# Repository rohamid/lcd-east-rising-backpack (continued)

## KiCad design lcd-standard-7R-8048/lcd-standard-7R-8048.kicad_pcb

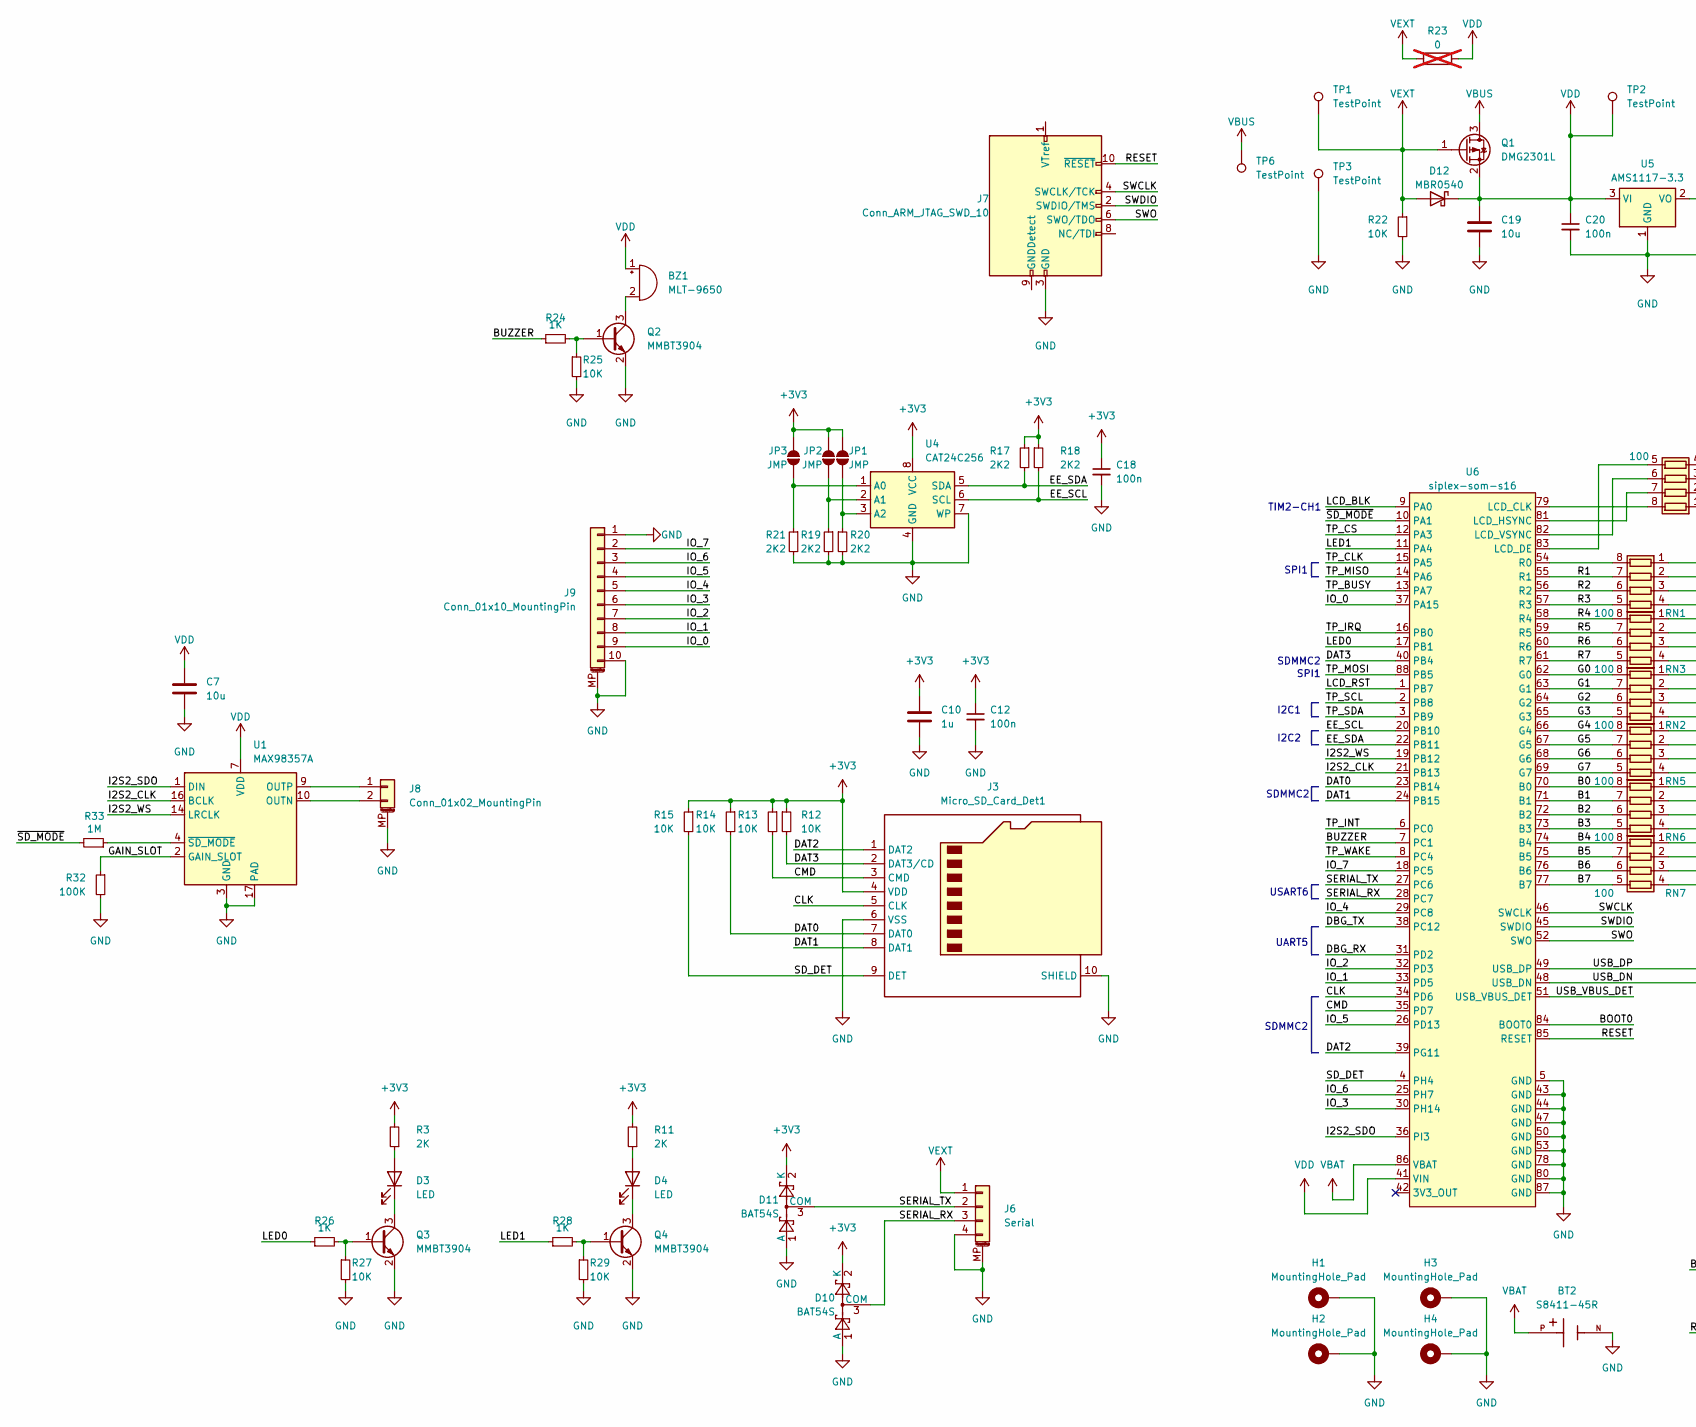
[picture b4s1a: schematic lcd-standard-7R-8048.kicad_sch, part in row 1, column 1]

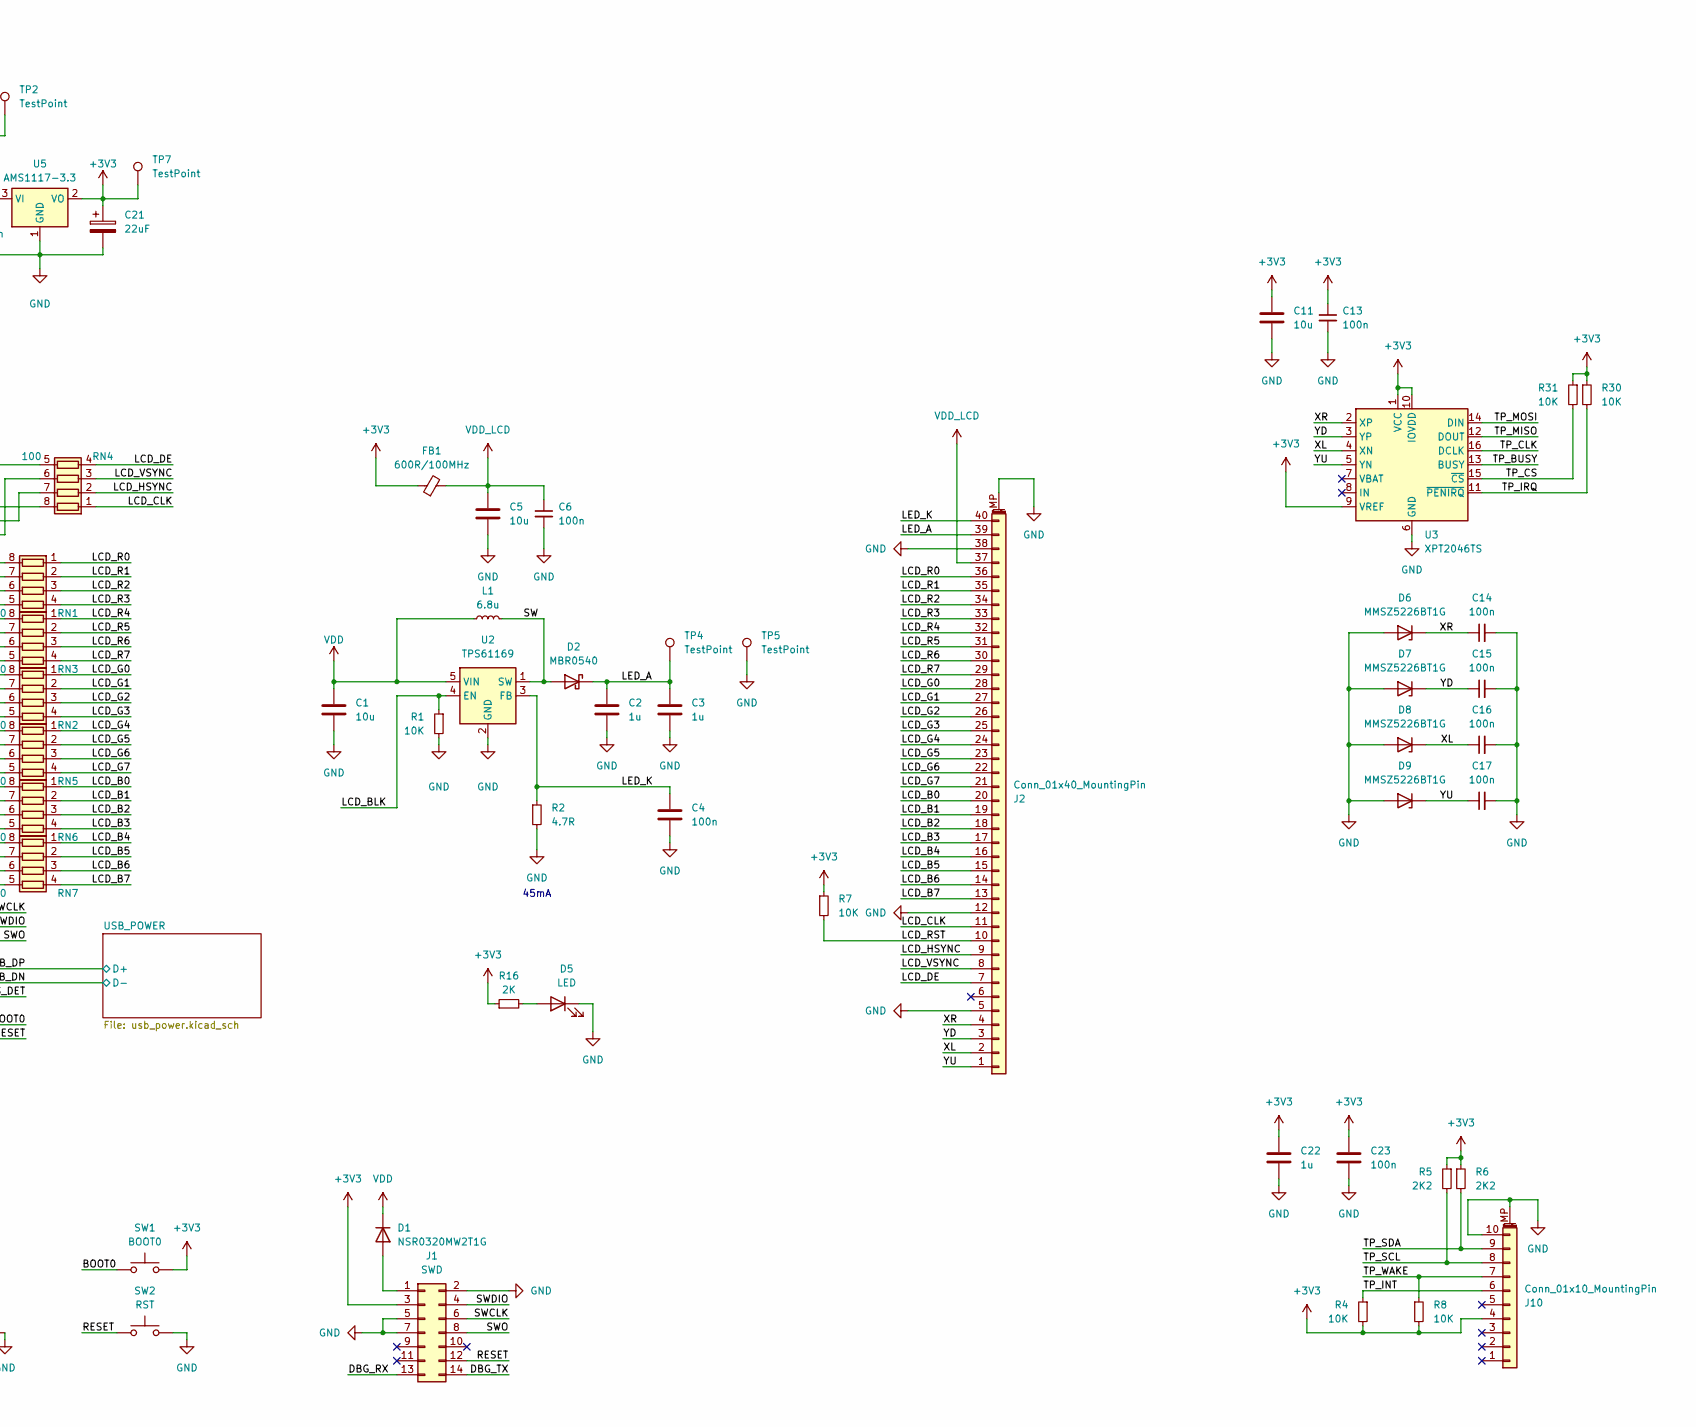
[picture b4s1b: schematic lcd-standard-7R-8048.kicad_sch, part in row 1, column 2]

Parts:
BT2: S8411-45R; CR1220-Batt-conn-S8411-45R
BZ1: MLT-9650; active-MLT-9650
C1: 10u; C_1206_3216Metric
C2, C3, C10, C22: 1u; C_0603_1608Metric
C4, C6, C13, C14, C15, C16, C17, C20, C23: 100n; C_0603_1608Metric
C5, C7, C11, C19: 10u; C_0805_2012Metric
C12, C18: 100n; C_0402_1005Metric
C21: 22uF; CP_EIA-3528-12_Kemet-T
D1: NSR0320MW2T1G; D_SOD-123
D2, D12: MBR0540; D_SOD-123
D3, D4, D5: LED; LED_0805_2012Metric
D6, D7, D8, D9: MMSZ5226BT1G; D_SOD-123
D10, D11: BAT54S; SOT-23
FB1: 600R/100MHz; C_0805_2012Metric
H1, H2, H3, H4: MountingHole_Pad; MountingHole_3.2mm_M3_Pad_Via
J1: SWD; PinHeader_2x07_P1.27mm_Vertical_SMD
J2: Conn_01x40_MountingPin; Omron_XF2M-4015-1A_1x40-1MP_P0.5mm_Horizontal
J3: Micro_SD_Card_Det1; SD-TF-115
J6: Serial; S4BXHSM4TBLFSN
J7: Conn_ARM_JTAG_SWD_10; Tag-Connect_TC2050-IDC-NL_2x05_P1.27mm_Vertical
J8: Conn_01x02_MountingPin; Hirose_DF13C_CL535-0402-2-51_1x02-1MP_P1.25mm_Vertical
J9: Conn_01x10_MountingPin; JST_SHL_SM10B-SHLS-TF_1x10-1MP_P1.00mm_Horizontal
J10: Conn_01x10_MountingPin; Hirose_FH12-10S-0.5SH_1x10-1MP_P0.50mm_Horizontal
JP1, JP2, JP3: JMP; SolderJumper-2_P1.3mm_Open_RoundedPad1.0x1.5mm
L1: 6.8u; L_Abracon_ASPI-4030S
Q1: DMG2301L; SOT-23
Q2, Q3, Q4: MMBT3904; SOT-23
R1, R4, R7, R8, R12, R13, R14, R15, R22, R25, R27, R29, R30, R31: 10K; R_0402_1005Metric
R2: 4.7R; R_0603_1608Metric
R3, R11, R16: 2K; R_0402_1005Metric
R5, R6, R17, R18, R19, R20, R21: 2K2; R_0402_1005Metric
R23: 0; R_1206_3216Metric; not fitted
R24, R26, R28: 1K; R_0402_1005Metric
R32: 100K; R_0402_1005Metric
R33: 1M; R_0402_1005Metric
RN1, RN2, RN3, RN4, RN5, RN6, RN7: 100; R_Array_Convex_4x0402
SW1: BOOT0; SW_SPST_PTS810
SW2: RST; SW_SPST_PTS810
TP1, TP2, TP3, TP4, TP5, TP6, TP7: TestPoint; TestPoint_Pad_D1.0mm
U1: MAX98357A; TQFN-16-1EP_3x3mm_P0.5mm_EP1.23x1.23mm
U2: TPS61169; SOT-23-5
U3: XPT2046TS; TSSOP-16_4.4x5mm_P0.65mm
U4: CAT24C256; SOIC-8_3.9x4.9mm_P1.27mm
U5: AMS1117-3.3; SOT-223-3_TabPin2
U6: siplex-som-s16

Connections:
+3V3: C10.1, C11.1, C12.1, C13.1, C18.1, C21.1, C22.1, C23.1, D10.2 (K), D11.2 (K), FB1.1, J1.3, J3.4 (VDD), J10.4, JP1.2 (B), JP2.2 (B), JP3.2 (B), R3.2, R4.2, R5.1, R6.1, R7.1, R8.2, R11.2, R12.1, R13.1, R14.1, R15.1, R16.1, R17.1, R18.1, R30.1, R31.1, SW1.2, TP7.1, U3.1 (VCC), U3.9 (VREF), U3.10 (IOVDD), U4.8 (VCC), U5.2 (VO)
/B0: RN6.8 (R1.2), U6.70 (B0)
/B1: RN6.7 (R2.2), U6.71 (B1)
/B2: RN6.6 (R3.2), U6.72 (B2)
/B3: RN6.5 (R4.2), U6.73 (B3)
/B4: RN7.8 (R1.2), U6.74 (B4)
/B5: RN7.7 (R2.2), U6.75 (B5)
/B6: RN7.6 (R3.2), U6.76 (B6)
/B7: RN7.5 (R4.2), U6.77 (B7)
/BOOT0: SW1.1, U6.84 (BOOT0)
/BUZZER: R24.1, U6.7 (PC1)
/CLK: J3.5 (CLK), U6.34 (PD6)
/CMD: J3.3 (CMD), R13.2, U6.35 (PD7)
/DAT0: J3.7 (DAT0), R14.2, U6.23 (PB14)
/DAT1: J3.8 (DAT1), U6.24 (PB15)
/DAT2: J3.1 (DAT2), U6.39 (PG11)
/DAT3: J3.2 (DAT3/CD), R12.2, U6.40 (PB4)
/DBG_RX: J1.13, U6.31 (PD2)
/DBG_TX: J1.14, U6.38 (PC12)
/EE_SCL: R18.2, U4.6 (SCL), U6.20 (PB10)
/EE_SDA: R17.2, U4.5 (SDA), U6.22 (PB11)
/G0: RN2.8 (R1.2), U6.62 (G0)
/G1: RN2.7 (R2.2), U6.63 (G1)
/G2: RN2.6 (R3.2), U6.64 (G2)
/G3: RN2.5 (R4.2), U6.65 (G3)
/G4: RN5.8 (R1.2), U6.66 (G4)
/G5: RN5.7 (R2.2), U6.67 (G5)
/G6: RN5.6 (R3.2), U6.68 (G6)
/G7: RN5.5 (R4.2), U6.69 (G7)
/GAIN_SLOT: R32.1, U1.2 (GAIN_SLOT)
/I2S2_CLK: U1.16 (BCLK), U6.21 (PB13)
/I2S2_SDO: U1.1 (DIN), U6.36 (PI3)
/I2S2_WS: U1.14 (LRCLK), U6.19 (PB12)
/IO_0: J9.9, U6.37 (PA15)
/IO_1: J9.8, U6.33 (PD5)
/IO_2: J9.7, U6.32 (PD3)
/IO_3: J9.6, U6.30 (PH14)
/IO_4: J9.5, U6.29 (PC8)
/IO_5: J9.4, U6.26 (PD13)
/IO_6: J9.3, U6.25 (PH7)
/IO_7: J9.2, U6.18 (PC5)
/LCD_B0: J2.20, RN6.1 (R1.1)
/LCD_B1: J2.19, RN6.2 (R2.1)
/LCD_B2: J2.18, RN6.3 (R3.1)
/LCD_B3: J2.17, RN6.4 (R4.1)
/LCD_B4: J2.16, RN7.1 (R1.1)
/LCD_B5: J2.15, RN7.2 (R2.1)
/LCD_B6: J2.14, RN7.3 (R3.1)
/LCD_B7: J2.13, RN7.4 (R4.1)
/LCD_BLK: R1.1, U2.4 (EN), U6.9 (PA0)
/LCD_CLK: J2.11, RN4.1 (R1.1)
/LCD_DE: J2.7, RN4.4 (R4.1)
/LCD_G0: J2.28, RN2.1 (R1.1)
/LCD_G1: J2.27, RN2.2 (R2.1)
/LCD_G2: J2.26, RN2.3 (R3.1)
/LCD_G3: J2.25, RN2.4 (R4.1)
/LCD_G4: J2.24, RN5.1 (R1.1)
/LCD_G5: J2.23, RN5.2 (R2.1)
/LCD_G6: J2.22, RN5.3 (R3.1)
/LCD_G7: J2.21, RN5.4 (R4.1)
/LCD_HSYNC: J2.9, RN4.2 (R2.1)
/LCD_R0: J2.36, RN1.1 (R1.1)
/LCD_R1: J2.35, RN1.2 (R2.1)
/LCD_R2: J2.34, RN1.3 (R3.1)
/LCD_R3: J2.33, RN1.4 (R4.1)
/LCD_R4: J2.32, RN3.1 (R1.1)
/LCD_R5: J2.31, RN3.2 (R2.1)
/LCD_R6: J2.30, RN3.3 (R3.1)
/LCD_R7: J2.29, RN3.4 (R4.1)
/LCD_RST: J2.10, R7.2, U6.1 (PB7)
/LCD_VSYNC: J2.8, RN4.3 (R3.1)
/LED0: R26.1, U6.17 (PB1)
/LED1: R28.1, U6.11 (PA4)
/LED_A: C2.1, C3.1, D2.1 (K), J2.39, TP4.1
/LED_K: C4.1, J2.40, R2.1, U2.3 (FB)
/R1: RN1.7 (R2.2), U6.55 (R1)
/R2: RN1.6 (R3.2), U6.56 (R2)
/R3: RN1.5 (R4.2), U6.57 (R3)
/R4: RN3.8 (R1.2), U6.58 (R4)
/R5: RN3.7 (R2.2), U6.59 (R5)
/R6: RN3.6 (R3.2), U6.60 (R6)
/R7: RN3.5 (R4.2), U6.61 (R7)
/RESET: J1.12, J7.10 (~RESET), SW2.1, U6.85 (RESET)
/SD_DET: J3.9 (DET), R15.2, U6.4 (PH4)
/SERIAL_RX: D10.3 (COM), J6.3, U6.28 (PC7)
/SERIAL_TX: D11.3 (COM), J6.2, U6.27 (PC6)
/SW: D2.2 (A), L1.2, U2.1 (SW)
/SWCLK: J1.6, J7.4 (SWCLK/TCK), U6.46 (SWCLK)
/SWDIO: J1.4, J7.2 (SWDIO/TMS), U6.45 (SWDIO)
/SWO: J1.8, J7.6 (SWO/TDO), U6.52 (SWO)
/TP_BUSY: U3.13 (BUSY), U6.13 (PA7)
/TP_CLK: U3.16 (DCLK), U6.15 (PA5)
/TP_CS: R31.2, U3.15 (~CS), U6.12 (PA3)
/TP_INT: J10.6, R4.1, U6.6 (PC0)
/TP_IRQ: R30.2, U3.11 (~PENIRQ), U6.16 (PB0)
/TP_MISO: U3.12 (DOUT), U6.14 (PA6)
/TP_MOSI: U3.14 (DIN), U6.88 (PB5)
/TP_SCL: J10.8, R5.2, U6.2 (PB8)
/TP_SDA: J10.9, R6.2, U6.3 (PB9)
/TP_WAKE: J10.7, R8.1, U6.8 (PC4)
/USB_DN: U6.48 (USB_DN); also elsewhere on the board
/USB_DP: U6.49 (USB_DP); also elsewhere on the board
/USB_VBUS_DET: U6.51 (USB_VBUS_DET)
/XL: C16.1, D8.1 (K), J2.2, U3.4 (XN)
/XR: C14.1, D6.1 (K), J2.4, U3.2 (XP)
/YD: C15.1, D7.1 (K), J2.3, U3.3 (YP)
/YU: C17.1, D9.1 (K), J2.1, U3.5 (YN)
/~SD_MODE: R33.2, U6.10 (PA1)
GND: BT2.N, C1.2, C2.2, C3.2, C4.2, C5.2, C6.2, C7.2, C10.2, C11.2, C12.2, C13.2, C14.2, C15.2, C16.2, C17.2, C18.2, C19.2, C20.2, C21.2, C22.2, C23.2, D5.1 (K), D6.2 (A), D7.2 (A), D8.2 (A), D9.2 (A), D10.1 (A), D11.1 (A), H1.1, H2.1, H3.1, H4.1, J1.2, J1.5, J1.7, J2.5, J2.12, J2.38, J2.MP (MountPin), J3.6 (VSS), J3.10 (SHIELD), J6.4, J6.MP (MountPin), J7.3 (GND), J7.5 (GND), J8.MP (MountPin), J9.1, J9.10, J9.MP (MountPin), J10.10, J10.MP (MountPin), Q2.2 (E), Q3.2 (E), Q4.2 (E), R1.2, R2.2, R19.2, R20.2, R21.2, R22.2, R25.2, R27.2, R29.2, R32.2, SW2.2, TP3.1, TP5.1, U1.3 (GND), U1.11 (GND), U1.15 (GND), U1.17 (PAD), U2.2 (GND), U3.6 (GND), U4.4 (GND), U4.7 (WP), U5.1 (GND), U6.5 (GND), U6.43 (GND), U6.44 (GND), U6.47 (GND), U6.50 (GND), U6.53 (GND), U6.78 (GND), U6.80 (GND), U6.87 (GND); also elsewhere on the board
unnamed: BZ1.2 (-), Q2.3 (C)
unnamed: D1.2 (A), J1.1
unnamed: D3.2 (A), R3.1
unnamed: D3.1 (K), Q3.3 (C)
unnamed: D4.2 (A), R11.1
unnamed: D4.1 (K), Q4.3 (C)
unnamed: D5.2 (A), R16.2
unnamed: J8.1, U1.9 (OUTP)
unnamed: J8.2, U1.10 (OUTN)
unnamed: JP1.1 (A), R20.1, U4.3 (A2)
unnamed: JP2.1 (A), R19.1, U4.2 (A1)
unnamed: JP3.1 (A), R21.1, U4.1 (A0)
unnamed: Q2.1 (B), R24.2, R25.1
unnamed: Q3.1 (B), R26.2, R27.1
unnamed: Q4.1 (B), R28.2, R29.1
unnamed: RN1.8 (R1.2), U6.54 (R0)
unnamed: RN4.8 (R1.2), U6.79 (LCD_CLK)
unnamed: RN4.7 (R2.2), U6.81 (LCD_HSYNC)
unnamed: RN4.6 (R3.2), U6.82 (LCD_VSYNC)
unnamed: RN4.5 (R4.2), U6.83 (LCD_DE)
unnamed: R33.1, U1.4 (~SD_MODE)
VBAT: BT2.P, U6.86 (VBAT)
VBUS: Q1.3 (D), TP6.1; also elsewhere on the board
VDD: BZ1.1 (+), C1.1, C7.1, C19.1, C20.1, D1.1 (K), D12.1 (K), L1.1, Q1.2 (S), R23.2, TP2.1, U1.7 (VDD), U1.8 (VDD), U2.5 (VIN), U5.3 (VI), U6.41 (VIN)
VDD_LCD: C5.1, C6.1, FB1.2, J2.37
VEXT: D12.2 (A), J6.1, Q1.1 (G), R22.1, R23.1, TP1.1

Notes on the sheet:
TIM2-CH1
USART6
SDMMC2
SPI1
I2C1
45mA
UART5
I2C2

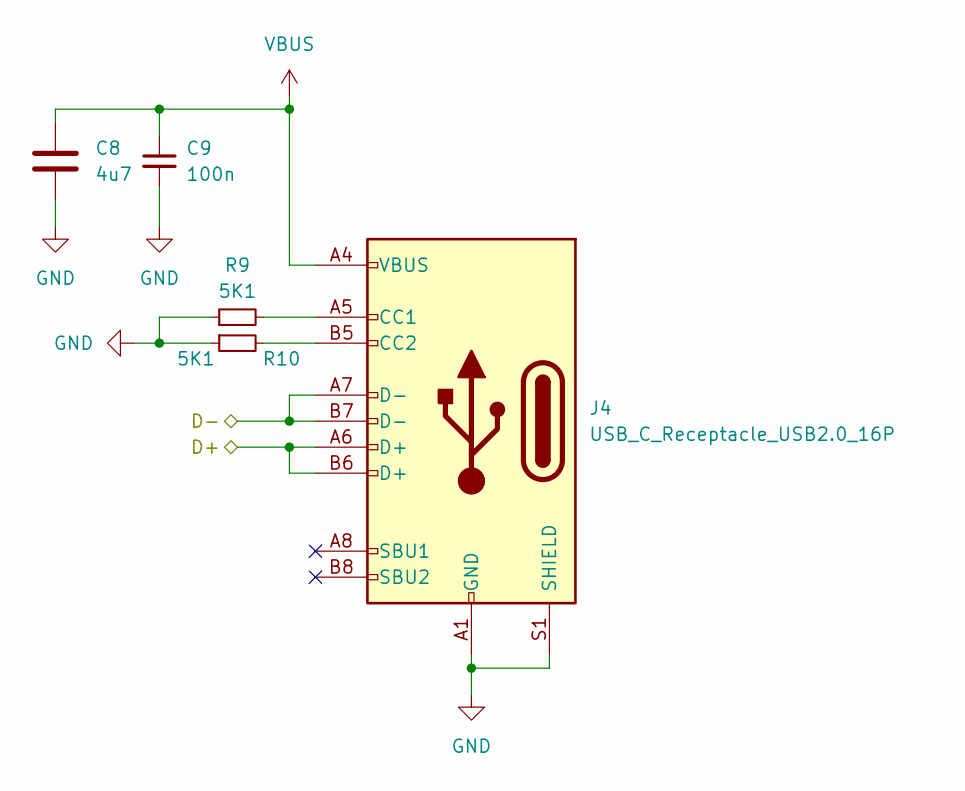
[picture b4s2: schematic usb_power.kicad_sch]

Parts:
C8: 4u7; C_0805_2012Metric
C9: 100n; C_0603_1608Metric
J4: USB_C_Receptacle_USB2.0_16P; USB_C_Receptacle_G-Switch_GT-USB-7010ASV
R9, R10: 5K1; R_0402_1005Metric

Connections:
/USB_DN: J4.A7 (D-), J4.B7 (D-); also elsewhere on the board
/USB_DP: J4.A6 (D+), J4.B6 (D+); also elsewhere on the board
GND: C8.2, C9.2, J4.A1 (GND), J4.A12 (GND), J4.B1 (GND), J4.B12 (GND), J4.S1 (SHIELD), R9.1, R10.1; also elsewhere on the board
unnamed: J4.A5 (CC1), R9.2
unnamed: J4.B5 (CC2), R10.2
VBUS: C8.1, C9.1, J4.A4 (VBUS), J4.A9 (VBUS), J4.B4 (VBUS), J4.B9 (VBUS); also elsewhere on the board

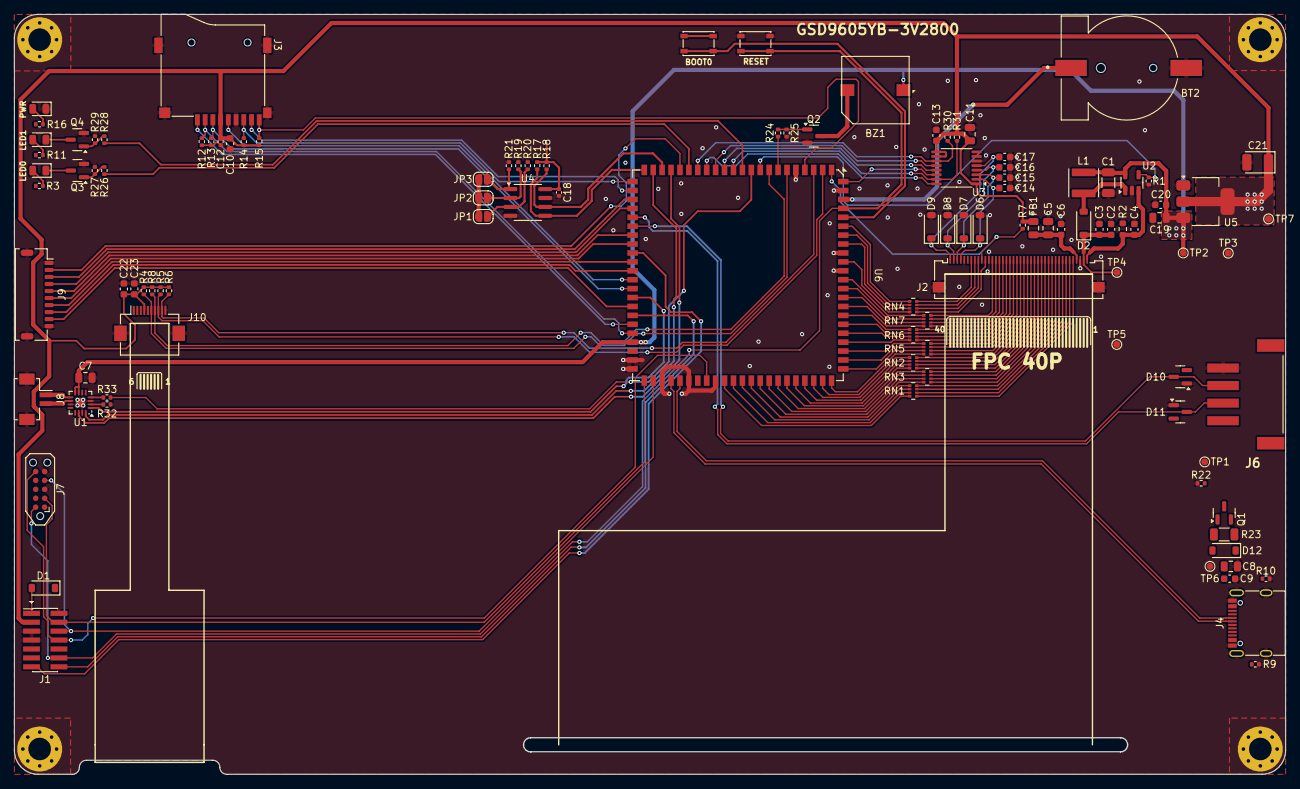
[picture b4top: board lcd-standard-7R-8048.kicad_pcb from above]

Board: 2 copper layers, 181.0 x 108.2 mm, 114 parts (0 on the bottom side), 136 nets.

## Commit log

2024-09-15 Finished all LCD dimension from east rising and tailor pixel
2024-09-16 Add LCD square 4-inch 480-480 & 720-720
2024-09-19 LCD 4inch 480-480 on progress
2024-09-19 Change SD card orientation
2024-09-20 Add standard 5inch and 7inch display both resistive and capacitive
2024-10-01 98% finished, st-link part left
2024-10-01 LCD 4inch 480x480 98% finished, st-link left
2024-10-02 Added Serial, Buzzer, AUX-IO, POWER switch, XPT2046, TAG-connect, EEPROM
2024-10-02 LCD 5 inch, Finished SD card, Touch, Buzzer etc, LCD Bar 3.4, Adding resistor on st-link, not finished yet
2024-10-03 Adding MAX98357 I2S mono Amplifier
2024-10-03 LCD 5inch, finished tracks, LCD square, Adding MAX98357A
2024-10-04 Add LCD standard 7inch
2024-10-06 Layouting LCD 7R, LED's and PWR tracks left
2024-10-07 Added sd_det tracks
2024-10-11 Slight changes
2024-10-13 Change LCD 5R to onboard MCU, cause separate boards are too expensive
2024-10-14 Change MCU to STM32H743
2024-10-14 Add 10P FPC for 5-inch Tailor pixel CTP
2024-10-15 Change 10P CTP to omron type
2024-10-16 Change pinout to the optimum usage
2024-10-17 Finished SDRAM, LCD (need checkup with CubeIDE), RTP touch controll
2024-10-18 Finsihed, need to touch up a bit
2024-10-19 Adding filter on MAX98357, TODO: Add more grounding vias
2024-11-26 Added 3.4inch bar LCD to the dimension
2025-01-03 Rebuild 4inch LCD with non SOM
2025-02-27 Add pinout for 5inch LCD Module
2025-04-16 Add QSPI Flash trace length matching to 5 inch LCD
2025-05-23 Change standoff dimension to match TJC LCD
2025-05-25 relocate SDRAM & QSPI Flash
2025-05-28 Replace QSPI Flash footprint
2025-06-01 relocate SDRAM
2025-06-09 LCD-5inch, SDRAM,QSPI,SDRCARD,EEPROM finished, 90% left
2025-06-26 finished tracks, need validation for ready to fabrication
2025-06-29 Need checkout the gerber before sending to JLCPCB
